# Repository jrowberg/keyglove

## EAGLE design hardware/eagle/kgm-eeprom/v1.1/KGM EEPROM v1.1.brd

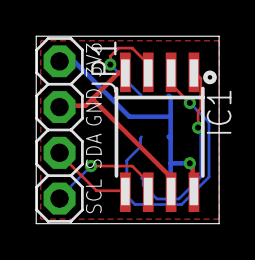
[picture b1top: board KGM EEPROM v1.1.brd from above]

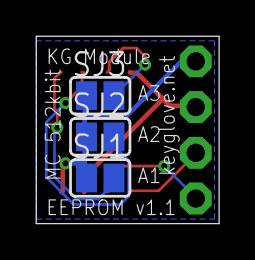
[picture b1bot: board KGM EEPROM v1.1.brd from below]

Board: 2 copper layers, 10.2 x 10.4 mm, 5 parts (3 on the bottom side), 7 nets.

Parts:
IC1: 24LC512SM; SO-08M
JP1: CONN; 1X04
SJ1: A0; SJ
SJ2: A1; SJ
SJ3: A2; SJ

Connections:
GND: IC1.4, IC1.7, JP1.2
unnamed: IC1.1, SJ1.2
unnamed: IC1.2, SJ2.2
unnamed: IC1.3, SJ3.2
SCL: IC1.6, JP1.4
SDA: IC1.5, JP1.3
VCC: IC1.8, JP1.1, SJ1.1, SJ2.1, SJ3.1
